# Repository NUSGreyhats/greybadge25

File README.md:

# greybadge25
GreyCTF 2025 Badge (Greymecha Army)

1. [Instruction Manual](https://docs.google.com/presentation/d/1nLdjBvxjxtfjGmfyWnxctUPe7XqL7leBmsDQaAjqEwk/edit?usp=sharing)
2. [Slides for Badge Talk](https://docs.google.com/presentation/d/1yoPuX5LA_Zj3ds3s_bZVRaBWZWmjrsSOJFy59PNaYqE/edit?usp=sharing)

## Repository Structure
```
.
├── firmware
│   ├── circuitpython_frozen_leaky.uf2  # CircuitPython firmware to flash
│   ├── ecp5                            # FPGA-related files                   
│   └── rp2350
│       ├── art                         # Greycat animation files (thanks shuqing!)
│       ├── filesystem                  # Filesystem to copy into CircuitPython (includes challenges)
│       ├── solutions                   # Solution scripts
│       └── src_chall                   # Raw challenge files for reference
├── hardware
│   ├── artwork                         # Artwork used on the PCB (thanks shuqing!)
│   ├── fpga_placement.svg              # High level reference for how the FPGA pins were used
│   ├── greybadge_pcb                   # KICAD files
│   ├── JLCPCB.kicad_dru
│   └── kicad_libraries
└── README.md
```

To view the schematic, find the pcb/prototype3 release and get the schematic pdf from there

## Firmware Set Up Guide
1. Connect the PCB to your computer. It will mount as a USB drive named RPI_RP2.
2. From the `/firmware` folder, drag & drop the file `circuitpython_frozen_leaky.uf2` onto the RPI_RP2 drive.
3. This should restart the badge and it will appear as a new USB drive called CIRCUITPYTHON.
4. Open `/firmware/rp2350/filesystem` on your computer and copy everything inside that folder to the CIRCUITPYTHON drive.
5. Your badge is set up!

## Hardware Ordering Guide
Refer to `Prototype 3 Order` under Releases.

Feel free to update the BOM to remove the oscillator for the FPGA as it is expensive and not strictly necessary.

Ordering on JLCPCB:
1. Upload the GERBER into the order page.
2. For the PCB Fab options, we recommend mostly using the defaults, but keep the following options in mind:
    - Finishing: HASL (HASL is fine, though we recommend ENIG for higher quantities as the extra cost scales well and is better for BGA soldering.)
    - To customize the main PCB colour, update the soldermask colour.
    - To have it assembled, tick the option below. You would likely want to choose to assemble both sides, which requires the standard assembly (not economic assembly).
3. Select the BOM/CPL if you chose to have it assembled.

There are several things you will need to order separately (and solder on).
1. Screen: [Taobao Link](https://item.taobao.com/item.htm?id=784228754299), choose the 焊接12P option.
2. Battery: You can either use a LIPO with JST-PH connector or solder 3x AA batteries.
    - LiPo Battery: [Taobao Link](https://item.taobao.com/item.htm?id=695205775685) We chose the 603040-750mAh option. If you want to have the plug rather than soldering the battery, contact the seller to install the 2.0-2P 反向公插 header (2.0mm pitch, 2 pin, reverse-orientation), which is essentially JST-PH, on the battery.
    - AA Battery Holder: [Taobao Link](https://detail.tmall.com/item.htm?id=533054527075).
    - 90 Degree Pinout Headers (or just solder wires)

## FPGA Tooling

A sample FPGA project is in `/firmware/ecp5/uart_coprocessor`. The tooling needed to be installed is as such

```
sudo apt install openFPGALoader # only needed if you use an external fpga jtag programmer
sudo apt install yosys
sudo apt install nextpnr-ecp5
sudo apt install fpga-trellis
```

Afterwards, you can just run `make clean` and `make` to generate the bitstream.

You can upload through the RP2350 in the `hardware.fpga` libraries

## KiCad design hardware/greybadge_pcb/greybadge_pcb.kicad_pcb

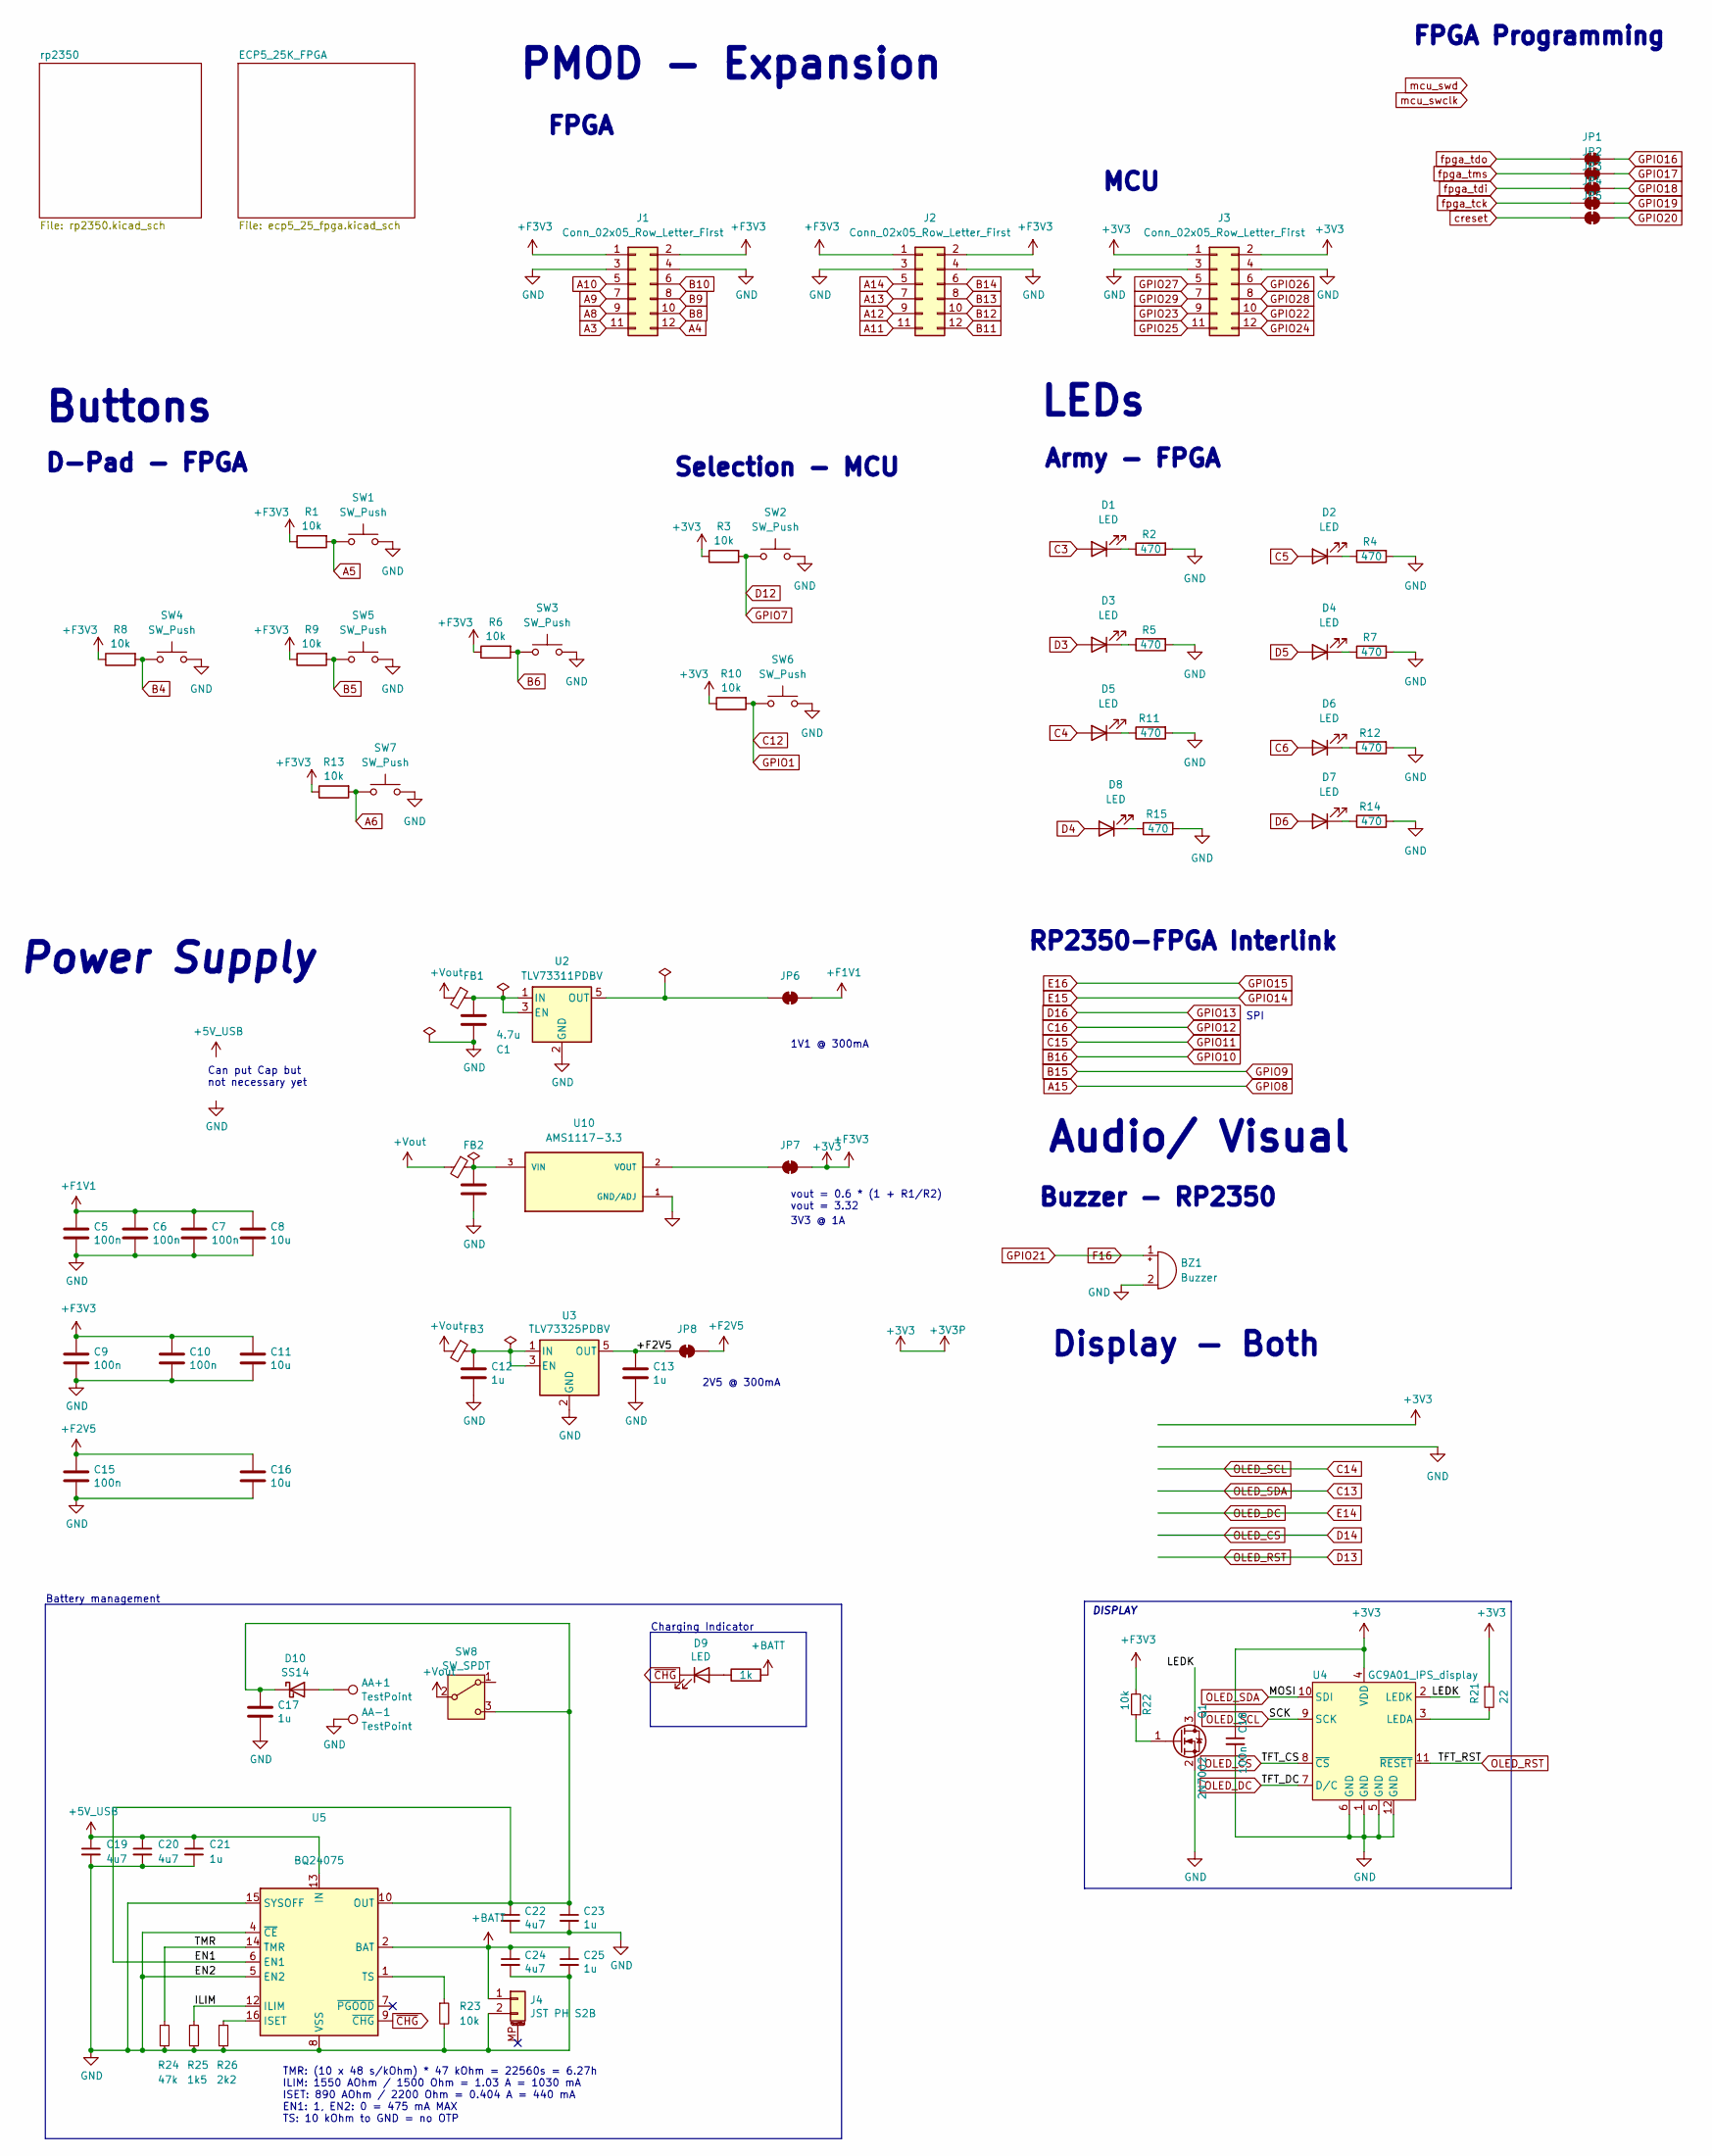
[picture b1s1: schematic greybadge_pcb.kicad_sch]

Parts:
AA+1: TestPoint; TestPoint_Pad_D1.5mm
AA-1: TestPoint; TestPoint_Pad_D1.5mm
BZ1: Buzzer; BUZ-SMD_4P-L7.5-W7.5-BR
C1, C3: 4.7u; C_0402_1005Metric
C5, C6, C7, C9, C10, C15, C18: 100n; C_0402_1005Metric
C8, C11, C16: 10u; C_0402_1005Metric
C12, C13, C17: 1u; C_0402_1005Metric
C19, C20, C22, C24: 4u7; C_0402_1005Metric; LCSC C23733
C21, C23, C25: 1u; C_0402_1005Metric; LCSC C52923
D1, D2, D3, D4, D5, D6, D7, D8: LED; LED_0603_1608Metric_Pad1.05x0.95mm_HandSolder
D9: LED; LED_0805_2012Metric
D10: SS14; D_SOD-123
FB1, FB2, FB3: Ferrite_Bead_Small; L_0805_2012Metric
J1, J2, J3: Conn_02x05_Row_Letter_First; PinSocket_2x06_P2.54mm_Horizontal
J4: JST PH S2B; JST_PH_S2B-PH-SM4-TB_1x02-1MP_P2.00mm_Horizontal; LCSC C505023
JP1, JP2, JP3, JP4, JP5, JP6, JP7, JP8: SolderJumper_2_Bridged; SolderJumper-2_P1.3mm_Bridged2Bar_RoundedPad1.0x1.5mm
Q1: 2N7002; SOT-23
R1, R3, R6, R8, R9, R10, R13: 10k; R_0603_1608Metric_Pad0.98x0.95mm_HandSolder
R2, R4, R5, R7, R11, R12, R14, R15: 470; R_0603_1608Metric_Pad0.98x0.95mm_HandSolder
R20: 1k; R_0805_2012Metric
R21: 22; R_0603_1608Metric
R22: 10k; R_0603_1608Metric
R23: 10k; R_0402_1005Metric; LCSC C25744
R24: 47k; R_0402_1005Metric; LCSC C25792
R25: 1k5; R_0402_1005Metric; LCSC C25867
R26: 2k2; R_0402_1005Metric; LCSC C25879
SW1, SW2, SW3, SW4, SW5, SW6, SW7: SW_Push; SW_Push_1P1T_XKB_TS-1187A
SW8: SW_SPDT; SW_SPDT_PCM12
U2: TLV73311PDBV; SOT-23-5
U3: TLV73325PDBV; SOT-23-5
U4: GC9A01_IPS_display
U5: BQ24075; VQFN-16-1EP_3x3mm_P0.5mm_EP1.6x1.6mm; LCSC C15464
U10: AMS1117-3.3; SOT-89-3_L4.5-W2.5-P1.50-LS4.2-BR; PARTREV N/A

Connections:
+3V3: C9.1, C10.1, C11.1, C18.1, J1.1, J1.2, J2.1, J2.2, J3.1, J3.2, JP7.2 (B), R1.1, R3.1, R6.1, R8.1, R9.1, R10.1, R13.1, R21.1, R22.2, U4.4 (VDD); also elsewhere on the board
+5V_USB: C19.1, C20.1, C21.1, U5.13 (IN); also elsewhere on the board
+BATT: C24.1, C25.1, J4.1, R20.2, U5.2 (BAT), U5.3 (BAT)
+F1V1: C5.1, C6.1, C7.1, C8.1, JP6.2 (B); also elsewhere on the board
+F2V5: C13.1, C15.1, C16.1, JP8.1 (A), JP8.2 (B), U3.5 (OUT); also elsewhere on the board
+Vout: FB1.2, FB2.2, FB3.2, SW8.2 (B)
/EN1: C17.1, C22.1, C23.1, D10.1 (K), SW8.3 (C), U5.6 (EN1), U5.10 (OUT), U5.11 (OUT)
/ILIM: R25.1, U5.12 (ILIM)
/LEDK: Q1.3 (D), U4.2 (LEDK)
/TMR: R24.1, U5.14 (TMR)
A3: J1.11; also elsewhere on the board
A4: J1.12; also elsewhere on the board
A5: R1.2, SW1.2; also elsewhere on the board
A6: R13.2, SW7.2; also elsewhere on the board
A8: J1.9; also elsewhere on the board
A9: J1.7; also elsewhere on the board
A10: J1.5; also elsewhere on the board
A11: J2.11; also elsewhere on the board
A12: J2.9; also elsewhere on the board
A13: J2.7; also elsewhere on the board
A14: J2.5; also elsewhere on the board
B4: R8.2, SW4.2; also elsewhere on the board
B5: R9.2, SW5.2; also elsewhere on the board
B6: R6.2, SW3.2; also elsewhere on the board
B8: J1.10; also elsewhere on the board
B9: J1.8; also elsewhere on the board
B10: J1.6; also elsewhere on the board
B11: J2.12; also elsewhere on the board
B12: J2.10; also elsewhere on the board
B13: J2.8; also elsewhere on the board
B14: J2.6; also elsewhere on the board
C3: D1.2 (A); also elsewhere on the board
C4: D5.2 (A); also elsewhere on the board
C5: D2.2 (A); also elsewhere on the board
C6: D6.2 (A); also elsewhere on the board
C12: R10.2, SW6.2; also elsewhere on the board
C13: U4.10 (SDI); also elsewhere on the board
C14: U4.9 (SCK); also elsewhere on the board
D3: D3.2 (A); also elsewhere on the board
D4: D8.2 (A); also elsewhere on the board
D5: D4.2 (A); also elsewhere on the board
D6: D7.2 (A); also elsewhere on the board
D12: R3.2, SW2.2; also elsewhere on the board
D13: U4.11 (~RESET); also elsewhere on the board
D14: U4.8 (~CS); also elsewhere on the board
E14: U4.7 (D/C); also elsewhere on the board
F16: BZ1.1 (+); also elsewhere on the board
GND: AA-1.1, BZ1.2 (-), C1.2, C3.2, C5.2, C6.2, C7.2, C8.2, C9.2, C10.2, C11.2, C12.2, C13.2, C15.2, C16.2, C17.2, C18.2, C19.2, C20.2, C21.2, C22.2, C23.2, C24.2, C25.2, J1.3, J1.4, J2.3, J2.4, J3.3, J3.4, J4.2, Q1.2 (S), R2.2, R4.2, R5.2, R7.2, R11.2, R12.2, R14.2, R15.2, R23.2, R24.2, R25.2, R26.2, SW1.1, SW2.1, SW3.1, SW4.1, SW5.1, SW6.1, SW7.1, U2.2 (GND), U3.2 (GND), U4.1 (GND), U4.5 (GND), U4.6 (GND), U4.12 (GND), U5.4 (~CE), U5.5 (EN2), U5.8 (VSS), U5.15 (SYSOFF), U5.17 (VSS), U10.1 (GND/ADJ); also elsewhere on the board
GPIO16: JP1.2 (B); also elsewhere on the board
GPIO17: JP2.2 (B); also elsewhere on the board
GPIO18: JP3.2 (B); also elsewhere on the board
GPIO19: JP4.2 (B); also elsewhere on the board
GPIO20: JP5.2 (B); also elsewhere on the board
GPIO22: J3.10; also elsewhere on the board
GPIO23: J3.9; also elsewhere on the board
GPIO24: J3.12; also elsewhere on the board
GPIO25: J3.11; also elsewhere on the board
GPIO26: J3.6; also elsewhere on the board
GPIO27: J3.5; also elsewhere on the board
GPIO28: J3.8; also elsewhere on the board
GPIO29: J3.7; also elsewhere on the board
unnamed: D1.1 (K), R2.1
unnamed: D2.1 (K), R4.1
unnamed: D3.1 (K), R5.1
unnamed: D4.1 (K), R7.1
unnamed: D5.1 (K), R11.1
unnamed: D6.1 (K), R12.1
unnamed: D7.1 (K), R14.1
unnamed: D8.1 (K), R15.1
unnamed: D9.2 (A), R20.1
unnamed: AA+1.1, D10.2 (A)
unnamed: JP6.1 (A), U2.5 (OUT)
unnamed: JP7.1 (A), U10.2 (VOUT)
unnamed: Q1.1 (G), R22.1
unnamed: C1.1, FB1.1, U2.1 (IN), U2.3 (EN)
unnamed: C12.1, FB3.1, U3.1 (IN), U3.3 (EN)
unnamed: R21.2, U4.3 (LEDA)
unnamed: R26.1, U5.16 (ISET)
unnamed: R23.1, U5.1 (TS)
unnamed: C3.1, FB2.1, U10.3 (VIN)
creset: JP5.1 (A); also elsewhere on the board
fpga_tck: JP4.1 (A); also elsewhere on the board
fpga_tdi: JP3.1 (A); also elsewhere on the board
fpga_tdo: JP1.1 (A); also elsewhere on the board
fpga_tms: JP2.1 (A); also elsewhere on the board
~CHG: D9.1 (K), U5.9 (~CHG)

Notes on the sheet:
Charging Indicator
3V3 @ 1A
SPI
Display - Both
Buzzer - RP2350
PMOD - Expansion
D-Pad - FPGA
Battery management
FPGA Programming
TMR: (10 x 48 s/kOhm) * 47 kOhm = 22560s = 6.27h ILIM: 1550 AOhm / 1500 Ohm = 1.03 A = 1030 mA ISET: 890 AOhm / 2200 Ohm = 0.404 A = 440 mA EN1: 1, EN2: 0 = 475 mA MAX TS: 10 kOhm to GND = no OTP
1V1 @ 300mA
DISPLAY
Army - FPGA
Selection - MCU
LEDs
MCU
Can put Cap but not necessary yet
Audio/ Visual
RP2350-FPGA Interlink
Power Supply
FPGA
Buttons
vout = 0.6 * (1 + R1/R2) vout = 3.32
2V5 @ 300mA

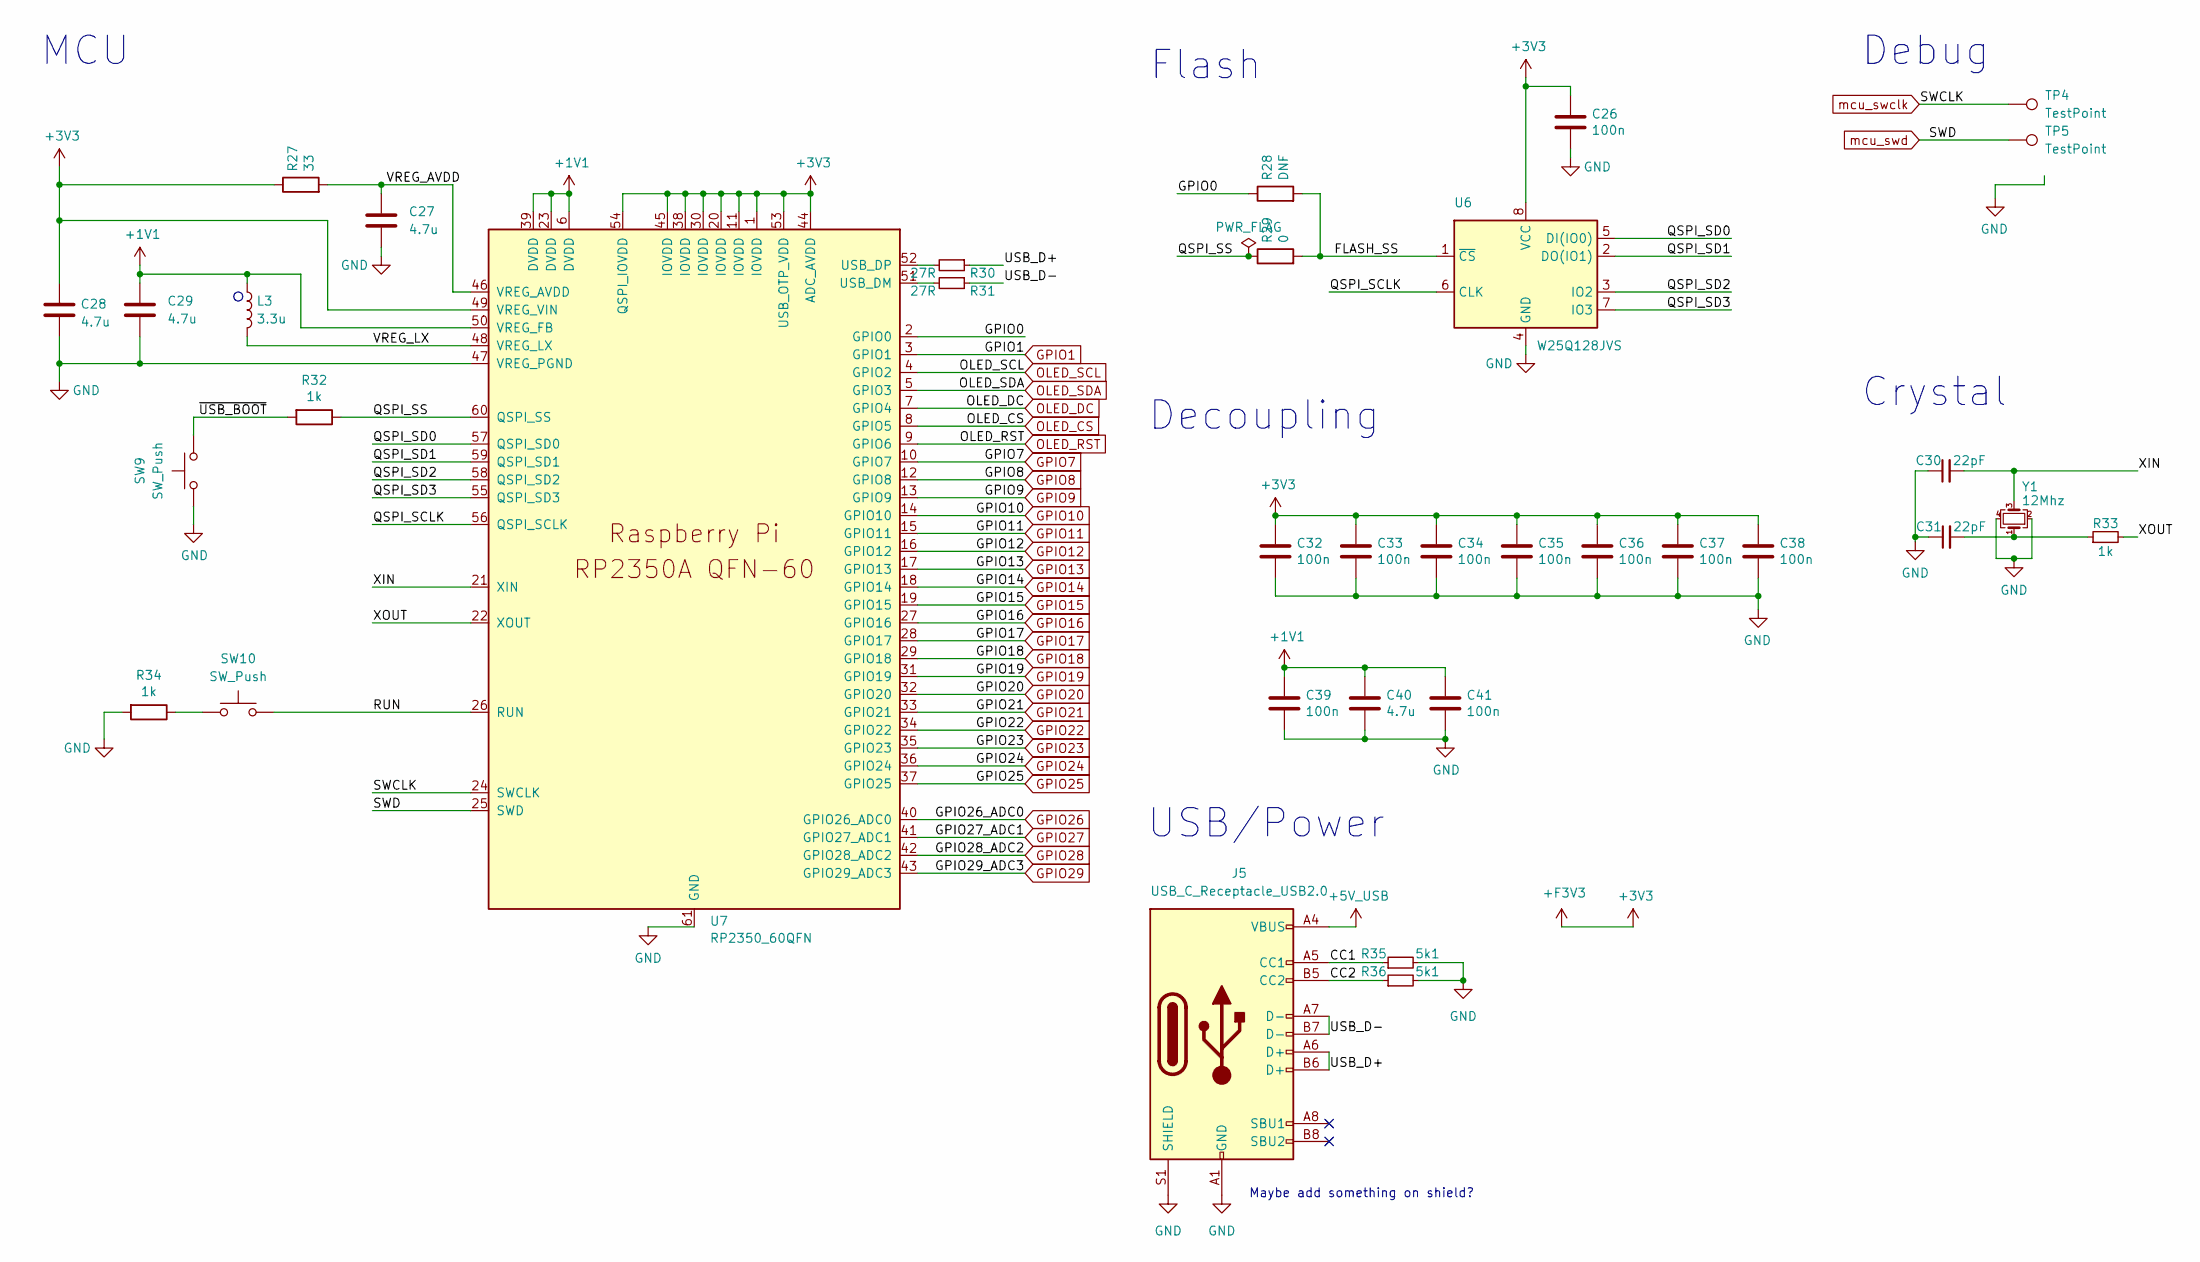
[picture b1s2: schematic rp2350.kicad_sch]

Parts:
C26, C32, C33, C34, C35, C36, C37, C38, C39, C41: 100n; C_0402_1005Metric
C27, C28, C29, C40: 4.7u; C_0402_1005Metric
C30, C31: 22pF; C_0402_1005Metric
J5: USB_C_Receptacle_USB2.0; USB_C_Receptacle_HRO_TYPE-C-31-M-12; LCSC C165948
L3: 3.3u; L_pol_2016
R27: 33; R_0402_1005Metric
R28: DNF; R_0402_1005Metric
R29: 0; R_0402_1005Metric
R30, R31: 27R; R_0402_1005Metric
R32, R33, R34: 1k; R_0402_1005Metric
R35, R36: 5k1; R_0402_1005Metric; LCSC C25905
SW9, SW10: SW_Push; SW_Push_1P1T_XKB_TS-1187A
TP4, TP5: TestPoint; TestPoint_Pad_D1.5mm
U6: W25Q128JVS; SOIC-8_5.3x5.3mm_P1.27mm
U7: RP2350_60QFN; RP2350-QFN-60-1EP_7x7_P0.4mm_EP3.4x3.4mm_ThermalVias
Y1: 12Mhz; Crystal_SMD_3225-4Pin_3.2x2.5mm

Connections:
+1V1: C29.1, C39.1, C40.1, C41.1, L3.1, U7.6 (DVDD), U7.23 (DVDD), U7.39 (DVDD), U7.50 (VREG_FB)
+3V3: C26.1, C28.1, C32.1, C33.1, C34.1, C35.1, C36.1, C37.1, C38.1, R27.1, U6.8 (VCC), U7.1 (IOVDD), U7.11 (IOVDD), U7.20 (IOVDD), U7.30 (IOVDD), U7.38 (IOVDD), U7.44 (ADC_AVDD), U7.45 (IOVDD), U7.49 (VREG_VIN), U7.53 (USB_OTP_VDD), U7.54 (QSPI_IOVDD); also elsewhere on the board
+5V_USB: J5.A4 (VBUS), J5.A9 (VBUS), J5.B4 (VBUS), J5.B9 (VBUS); also elsewhere on the board
/rp2350/CC1: J5.A5 (CC1), R35.1
/rp2350/CC2: J5.B5 (CC2), R36.1
/rp2350/FLASH_SS: R28.2, R29.2, U6.1 (~CS)
/rp2350/GPIO0: R28.1, U7.2 (GPIO0)
/rp2350/QSPI_SCLK: U6.6 (CLK), U7.56 (QSPI_SCLK)
/rp2350/QSPI_SD0: U6.5 (DI(IO0)), U7.57 (QSPI_SD0)
/rp2350/QSPI_SD1: U6.2 (DO(IO1)), U7.59 (QSPI_SD1)
/rp2350/QSPI_SD2: U6.3 (IO2), U7.58 (QSPI_SD2)
/rp2350/QSPI_SD3: U6.7 (IO3), U7.55 (QSPI_SD3)
/rp2350/QSPI_SS: R29.1, R32.1, U7.60 (QSPI_SS)
/rp2350/RUN: SW10.1, U7.26 (RUN)
/rp2350/USB_D+: J5.A6 (D+), J5.B6 (D+), R30.1
/rp2350/USB_D-: J5.A7 (D-), J5.B7 (D-), R31.1
/rp2350/VREG_AVDD: C27.1, R27.2, U7.46 (VREG_AVDD)
/rp2350/VREG_LX: L3.2, U7.48 (VREG_LX)
/rp2350/XIN: C30.2, U7.21 (XIN), Y1.3
/rp2350/XOUT: R33.2, U7.22 (XOUT)
/rp2350/~USB_BOOT: R32.2, SW9.1
C12: U7.3 (GPIO1); also elsewhere on the board
C13: U7.5 (GPIO3); also elsewhere on the board
C14: U7.4 (GPIO2); also elsewhere on the board
D12: U7.10 (GPIO7); also elsewhere on the board
D13: U7.9 (GPIO6); also elsewhere on the board
D14: U7.8 (GPIO5); also elsewhere on the board
E14: U7.7 (GPIO4); also elsewhere on the board
F16: U7.33 (GPIO21); also elsewhere on the board
GND: C26.2, C27.2, C28.2, C29.2, C30.1, C31.1, C32.2, C33.2, C34.2, C35.2, C36.2, C37.2, C38.2, C39.2, C40.2, C41.2, J5.A1 (GND), J5.A12 (GND), J5.B1 (GND), J5.B12 (GND), J5.S1 (SHIELD), R34.2, R35.2, R36.2, SW9.2, U6.4 (GND), U7.47 (VREG_PGND), U7.61 (GND), Y1.2, Y1.4; also elsewhere on the board
GPIO16: U7.27 (GPIO16); also elsewhere on the board
GPIO17: U7.28 (GPIO17); also elsewhere on the board
GPIO18: U7.29 (GPIO18); also elsewhere on the board
GPIO19: U7.31 (GPIO19); also elsewhere on the board
GPIO20: U7.32 (GPIO20); also elsewhere on the board
GPIO22: U7.34 (GPIO22); also elsewhere on the board
GPIO23: U7.35 (GPIO23); also elsewhere on the board
GPIO24: U7.36 (GPIO24); also elsewhere on the board
GPIO25: U7.37 (GPIO25); also elsewhere on the board
GPIO26: U7.40 (GPIO26_ADC0); also elsewhere on the board
GPIO27: U7.41 (GPIO27_ADC1); also elsewhere on the board
GPIO28: U7.42 (GPIO28_ADC2); also elsewhere on the board
GPIO29: U7.43 (GPIO29_ADC3); also elsewhere on the board
unnamed: C31.2, R33.1, Y1.1
unnamed: R34.1, SW10.2
unnamed: R31.2, U7.51 (USB_DM)
unnamed: R30.2, U7.52 (USB_DP)
mcu_swclk: TP4.1, U7.24 (SWCLK)
mcu_swd: TP5.1, U7.25 (SWD)

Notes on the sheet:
Debug
Crystal
Flash
USB/Power
Maybe add something on shield?
MCU
Decoupling

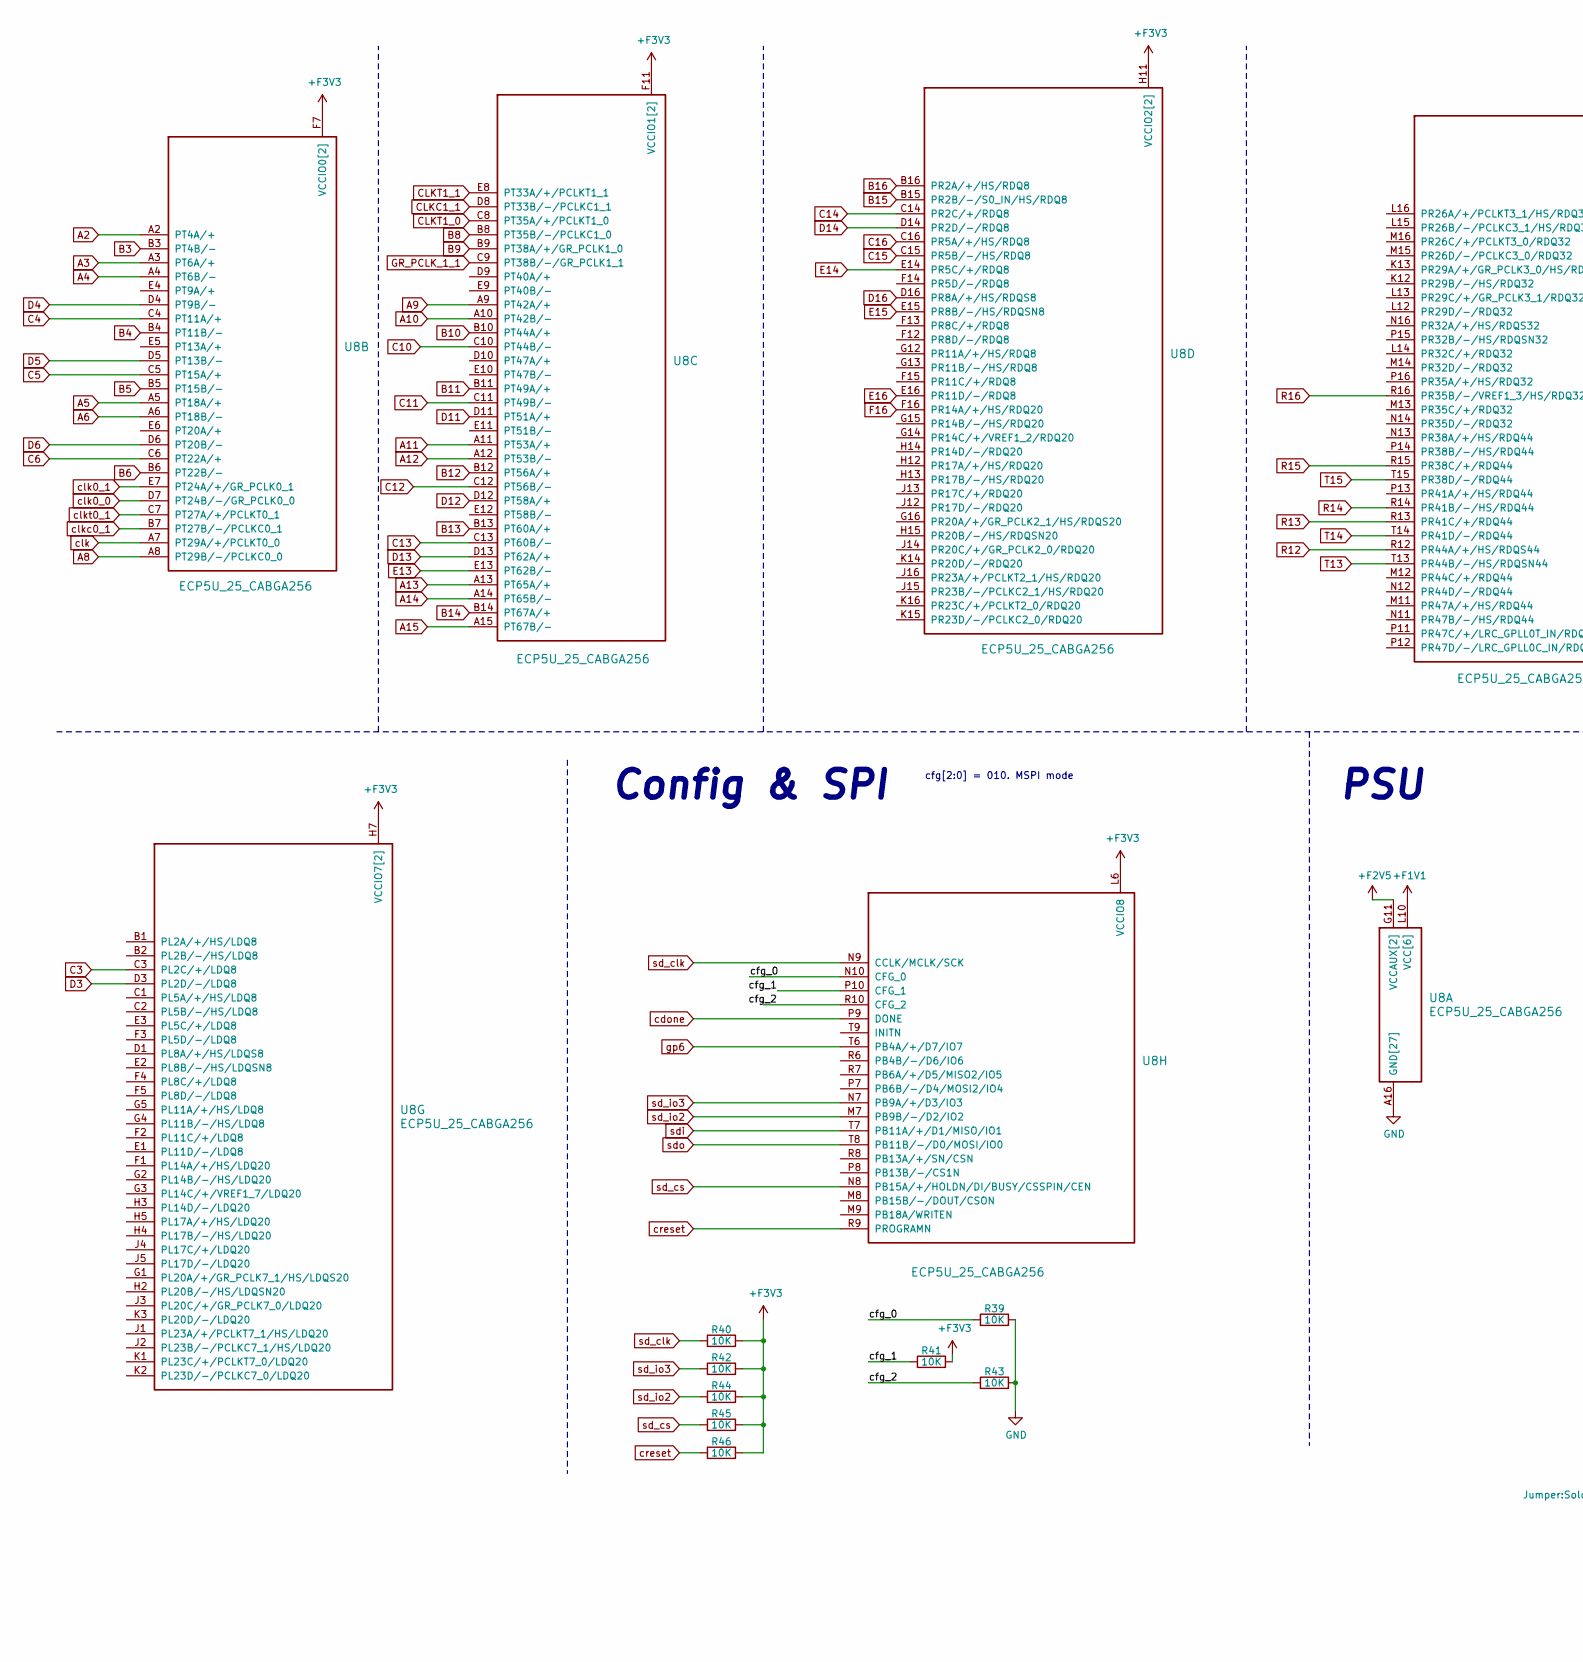
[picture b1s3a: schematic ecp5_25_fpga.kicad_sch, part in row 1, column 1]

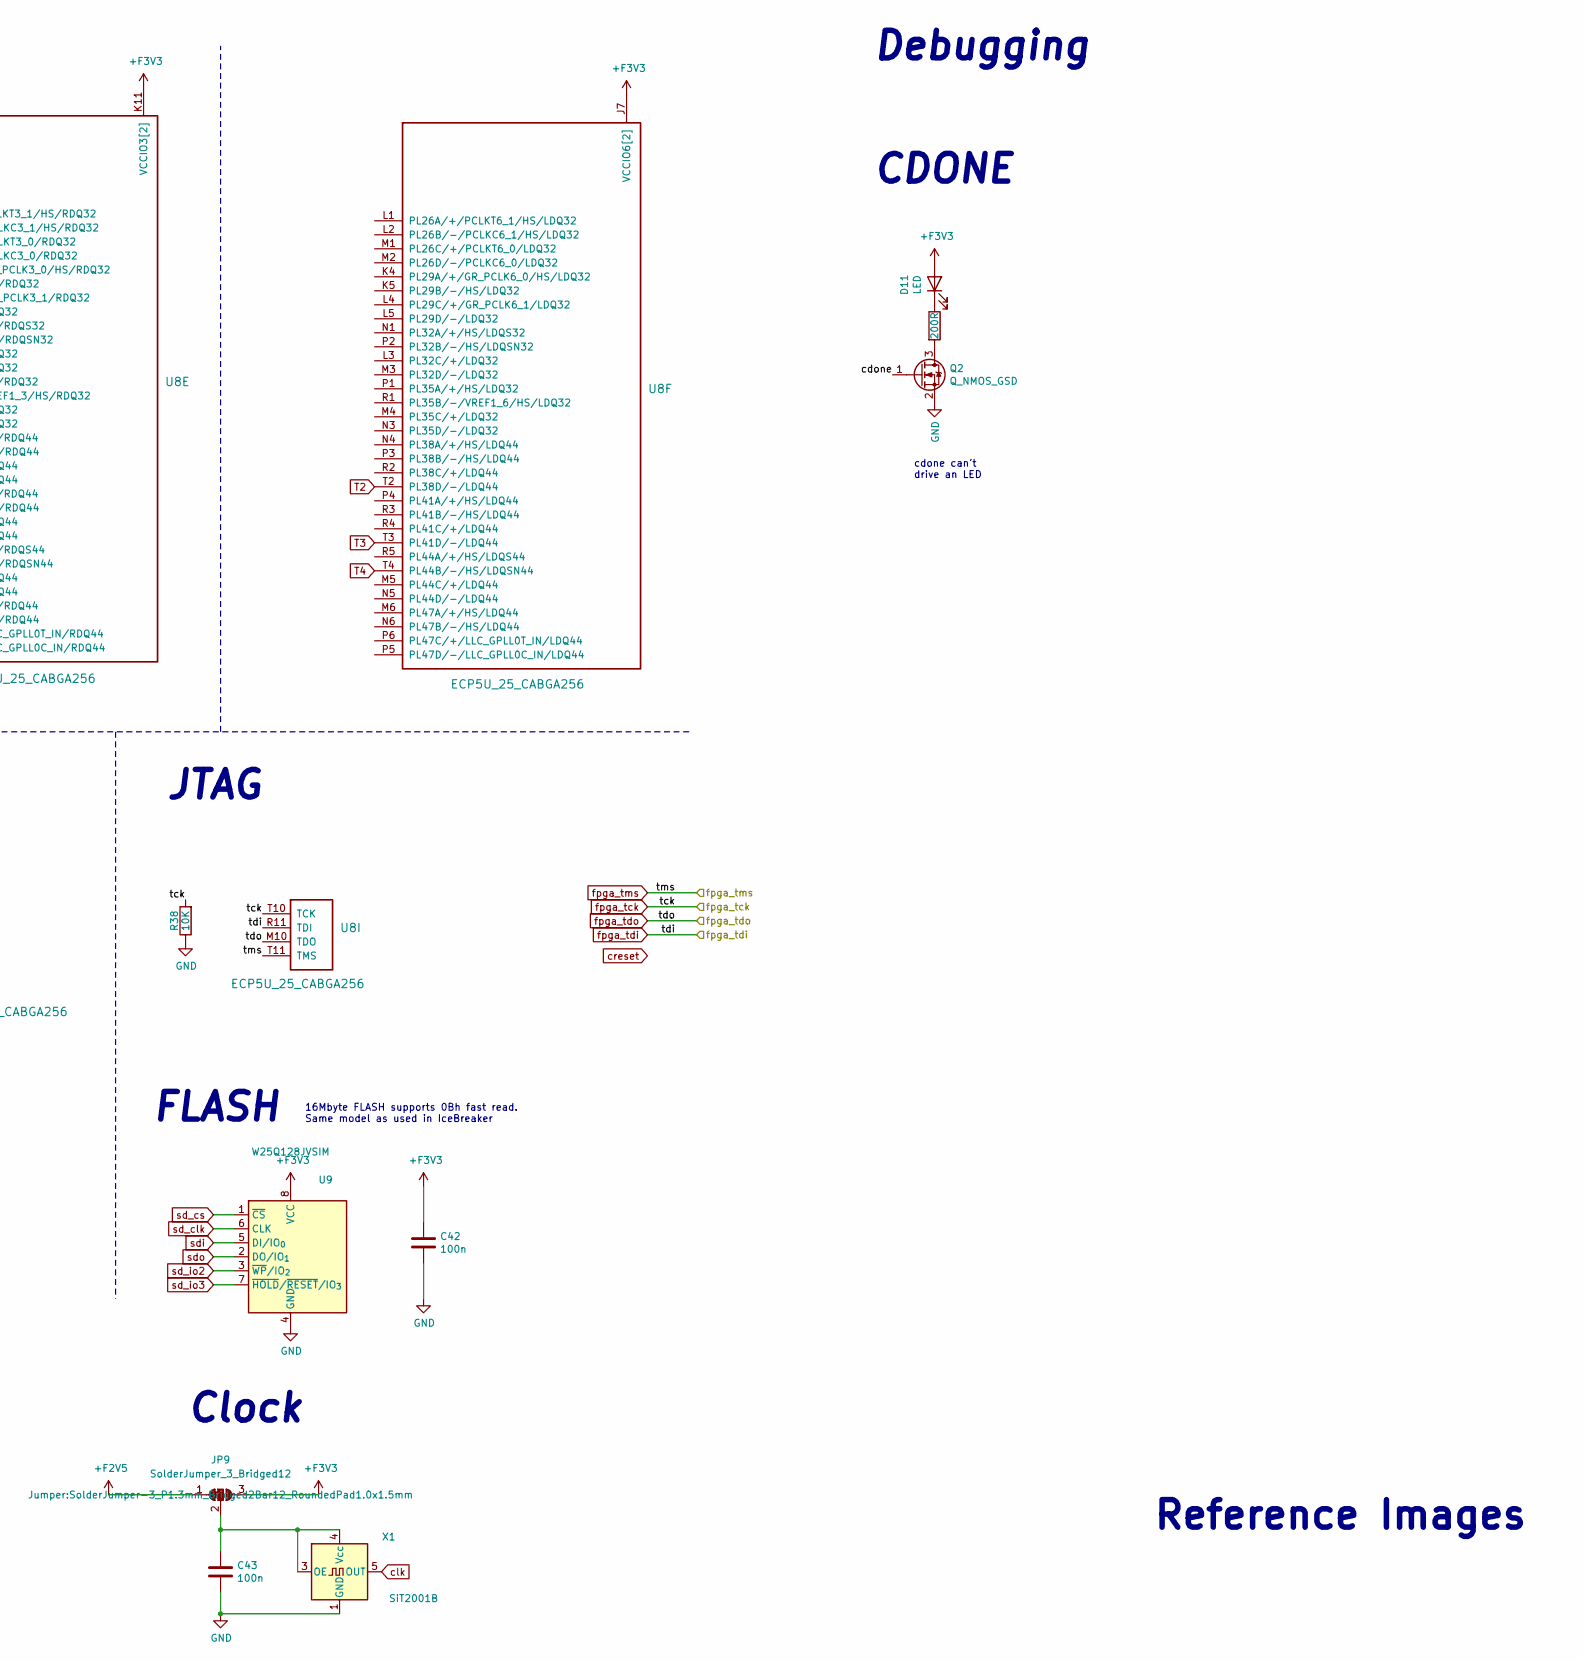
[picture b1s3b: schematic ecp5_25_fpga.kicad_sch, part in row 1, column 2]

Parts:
C42, C43: 100n; C_0402_1005Metric
D11: LED; LED_0805_2012Metric
JP9: SolderJumper_3_Bridged12; SolderJumper-3_P1.3mm_Bridged2Bar12_RoundedPad1.0x1.5mm
Q2: Q_NMOS_GSD; SOT-23
R37: 200R; R_0805_2012Metric
R38, R39, R40, R41, R42, R43, R44, R45, R46: 10K; R_0603_1608Metric_Pad0.98x0.95mm_HandSolder
U8: ECP5U_25_CABGA256; BGA-256_14.0x14.0mm_Layout16x16_P0.8mm_Ball0.45mm_Pad0.32mm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
U9: W25Q128JVSIM; SOIC-8_5.3x5.3mm_P1.27mm
X1: SiT2001B; SOT-23-5

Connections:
+3V3: C42.1, D11.2 (A), JP9.3 (B), R40.2, R41.2, R42.2, R44.2, R45.2, R46.2, U8.F6 (VCCIO0[2]), U8.F7 (VCCIO0[2]), U8.F10 (VCCIO1[2]), U8.F11 (VCCIO1[2]), U8.H6 (VCCIO7[2]), U8.H7 (VCCIO7[2]), U8.H11 (VCCIO2[2]), U8.J6 (VCCIO6[2]), U8.J7 (VCCIO6[2]), U8.J11 (VCCIO2[2]), U8.K11 (VCCIO3[2]), U8.L6 (VCCIO8), U8.L11 (VCCIO3[2]), U9.8 (VCC); also elsewhere on the board
+F1V1: U8.G6 (VCC[6]), U8.G7 (VCC[6]), U8.G9 (VCC[6]), U8.L8 (VCC[6]), U8.L9 (VCC[6]), U8.L10 (VCC[6]); also elsewhere on the board
+F2V5: JP9.1 (A), U8.G11 (VCCAUX[2]), U8.L7 (VCCAUX[2]); also elsewhere on the board
/ECP5_25K_FPGA/cfg_0: R39.1, U8.N10 (CFG_0)
/ECP5_25K_FPGA/cfg_1: R41.1, U8.P10 (CFG_1)
/ECP5_25K_FPGA/cfg_2: R43.1, U8.R10 (CFG_2)
A2: U8.A2 (PT4A/+)
A3: U8.A3 (PT6A/+); also elsewhere on the board
A4: U8.A4 (PT6B/-); also elsewhere on the board
A5: U8.A5 (PT18A/+); also elsewhere on the board
A6: U8.A6 (PT18B/-); also elsewhere on the board
A8: U8.A8 (PT29B/-/PCLKC0_0); also elsewhere on the board
A9: U8.A9 (PT42A/+); also elsewhere on the board
A10: U8.A10 (PT42B/-); also elsewhere on the board
A11: U8.A11 (PT53A/+); also elsewhere on the board
A12: U8.A12 (PT53B/-); also elsewhere on the board
A13: U8.A13 (PT65A/+); also elsewhere on the board
A14: U8.A14 (PT65B/-); also elsewhere on the board
B3: U8.B3 (PT4B/-)
B4: U8.B4 (PT11B/-); also elsewhere on the board
B5: U8.B5 (PT15B/-); also elsewhere on the board
B6: U8.B6 (PT22B/-); also elsewhere on the board
B8: U8.B8 (PT35B/-/PCLKC1_0); also elsewhere on the board
B9: U8.B9 (PT38A/+/GR_PCLK1_0); also elsewhere on the board
B10: U8.B10 (PT44A/+); also elsewhere on the board
B11: U8.B11 (PT49A/+); also elsewhere on the board
B12: U8.B12 (PT56A/+); also elsewhere on the board
B13: U8.B13 (PT60A/+); also elsewhere on the board
B14: U8.B14 (PT67A/+); also elsewhere on the board
C3: U8.C3 (PL2C/+/LDQ8); also elsewhere on the board
C4: U8.C4 (PT11A/+); also elsewhere on the board
C5: U8.C5 (PT15A/+); also elsewhere on the board
C6: U8.C6 (PT22A/+); also elsewhere on the board
C10: U8.C10 (PT44B/-)
C11: U8.C11 (PT49B/-)
C12: U8.C12 (PT56B/-); also elsewhere on the board
C13: U8.C13 (PT60B/-); also elsewhere on the board
C14: U8.C14 (PR2C/+/RDQ8); also elsewhere on the board
CLKC1_1: U8.D8 (PT33B/-/PCLKC1_1)
CLKT1_0: U8.C8 (PT35A/+/PCLKT1_0)
CLKT1_1: U8.E8 (PT33A/+/PCLKT1_1)
D3: U8.D3 (PL2D/-/LDQ8); also elsewhere on the board
D4: U8.D4 (PT9B/-); also elsewhere on the board
D5: U8.D5 (PT13B/-); also elsewhere on the board
D6: U8.D6 (PT20B/-); also elsewhere on the board
D11: U8.D11 (PT51A/+)
D12: U8.D12 (PT58A/+); also elsewhere on the board
D13: U8.D13 (PT62A/+); also elsewhere on the board
D14: U8.D14 (PR2D/-/RDQ8); also elsewhere on the board
E13: U8.E13 (PT62B/-)
E14: U8.E14 (PR5C/+/RDQ8); also elsewhere on the board
F16: U8.F16 (PR14A/+/HS/RDQ20); also elsewhere on the board
GND: C42.2, C43.2, Q2.2 (S), R38.1, R39.2, R43.2, U8.A1 (GND[27]), U8.A16 (GND[27]), U8.D2 (GND[27]), U8.D15 (GND[27]), U8.F8 (GND[27]), U8.F9 (GND[27]), U8.G8 (GND[27]), U8.G10 (GND[27]), U8.H1 (GND[27]), U8.H8 (GND[27]), U8.H9 (GND[27]), U8.H10 (GND[27]), U8.H16 (GND[27]), U8.J8 (GND[27]), U8.J9 (GND[27]), U8.J10 (GND[27]), U8.K6 (GND[27]), U8.K7 (GND[27]), U8.K8 (GND[27]), U8.K9 (GND[27]), U8.K10 (GND[27]), U8.N2 (GND[27]), U8.N15 (GND[27]), U8.T1 (GND[27]), U8.T5 (GND[27]), U8.T12 (GND[27]), U8.T16 (GND[27]), U9.4 (GND), X1.1 (GND); also elsewhere on the board
GR_PCLK_1_1: U8.C9 (PT38B/-/GR_PCLK1_1)
unnamed: D11.1 (K), R37.1
unnamed: C43.1, JP9.2 (C), X1.3 (OE), X1.4 (Vcc)
unnamed: Q2.3 (D), R37.2
R12: U8.R12 (PR44A/+/HS/RDQS44)
R13: U8.R13 (PR41C/+/RDQ44)
R14: U8.R14 (PR41B/-/HS/RDQ44)
R15: U8.R15 (PR38C/+/RDQ44)
R16: U8.R16 (PR35B/-/VREF1_3/HS/RDQ32)
T2: U8.T2 (PL38D/-/LDQ44)
T3: U8.T3 (PL41D/-/LDQ44)
T4: U8.T4 (PL44B/-/HS/LDQSN44)
T13: U8.T13 (PR44B/-/HS/RDQSN44)
T14: U8.T14 (PR41D/-/RDQ44)
T15: U8.T15 (PR38D/-/RDQ44)
cdone: Q2.1 (G), U8.P9 (DONE)
clk: U8.A7 (PT29A/+/PCLKT0_0), X1.5 (OUT)
clk0_0: U8.D7 (PT24B/-/GR_PCLK0_0)
clk0_1: U8.E7 (PT24A/+/GR_PCLK0_1)
clkc0_1: U8.B7 (PT27B/-/PCLKC0_1)
clkt0_1: U8.C7 (PT27A/+/PCLKT0_1)
creset: R46.1, U8.R9 (PROGRAMN); also elsewhere on the board
fpga_tck: R38.2, U8.T10 (TCK); also elsewhere on the board
fpga_tdi: U8.R11 (TDI); also elsewhere on the board
fpga_tdo: U8.M10 (TDO); also elsewhere on the board
fpga_tms: U8.T11 (TMS); also elsewhere on the board
gp6: U8.T6 (PB4A/+/D7/IO7)
sd_clk: R40.1, U8.N9 (CCLK/MCLK/SCK), U9.6 (CLK)
sd_cs: R45.1, U8.N8 (PB15A/+/HOLDN/DI/BUSY/CSSPIN/CEN), U9.1 (~CS)
sd_io2: R44.1, U8.M7 (PB9B/-/D2/IO2), U9.3 (~WP/IO_{2})
sd_io3: R42.1, U8.N7 (PB9A/+/D3/IO3), U9.7 (~HOLD/~RESET/IO_{3})
sdi: U8.T7 (PB11A/+/D1/MISO/IO1), U9.5 (DI/IO_{0})
sdo: U8.T8 (PB11B/-/D0/MOSI/IO0), U9.2 (DO/IO_{1})

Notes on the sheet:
16Mbyte FLASH supports 0Bh fast read. Same model as used in IceBreaker
Config & SPI
PSU
Debugging
Reference Images
cfg[2:0] = 010. MSPI mode
CDONE
FLASH
cdone can't drive an LED
JTAG
Clock

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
